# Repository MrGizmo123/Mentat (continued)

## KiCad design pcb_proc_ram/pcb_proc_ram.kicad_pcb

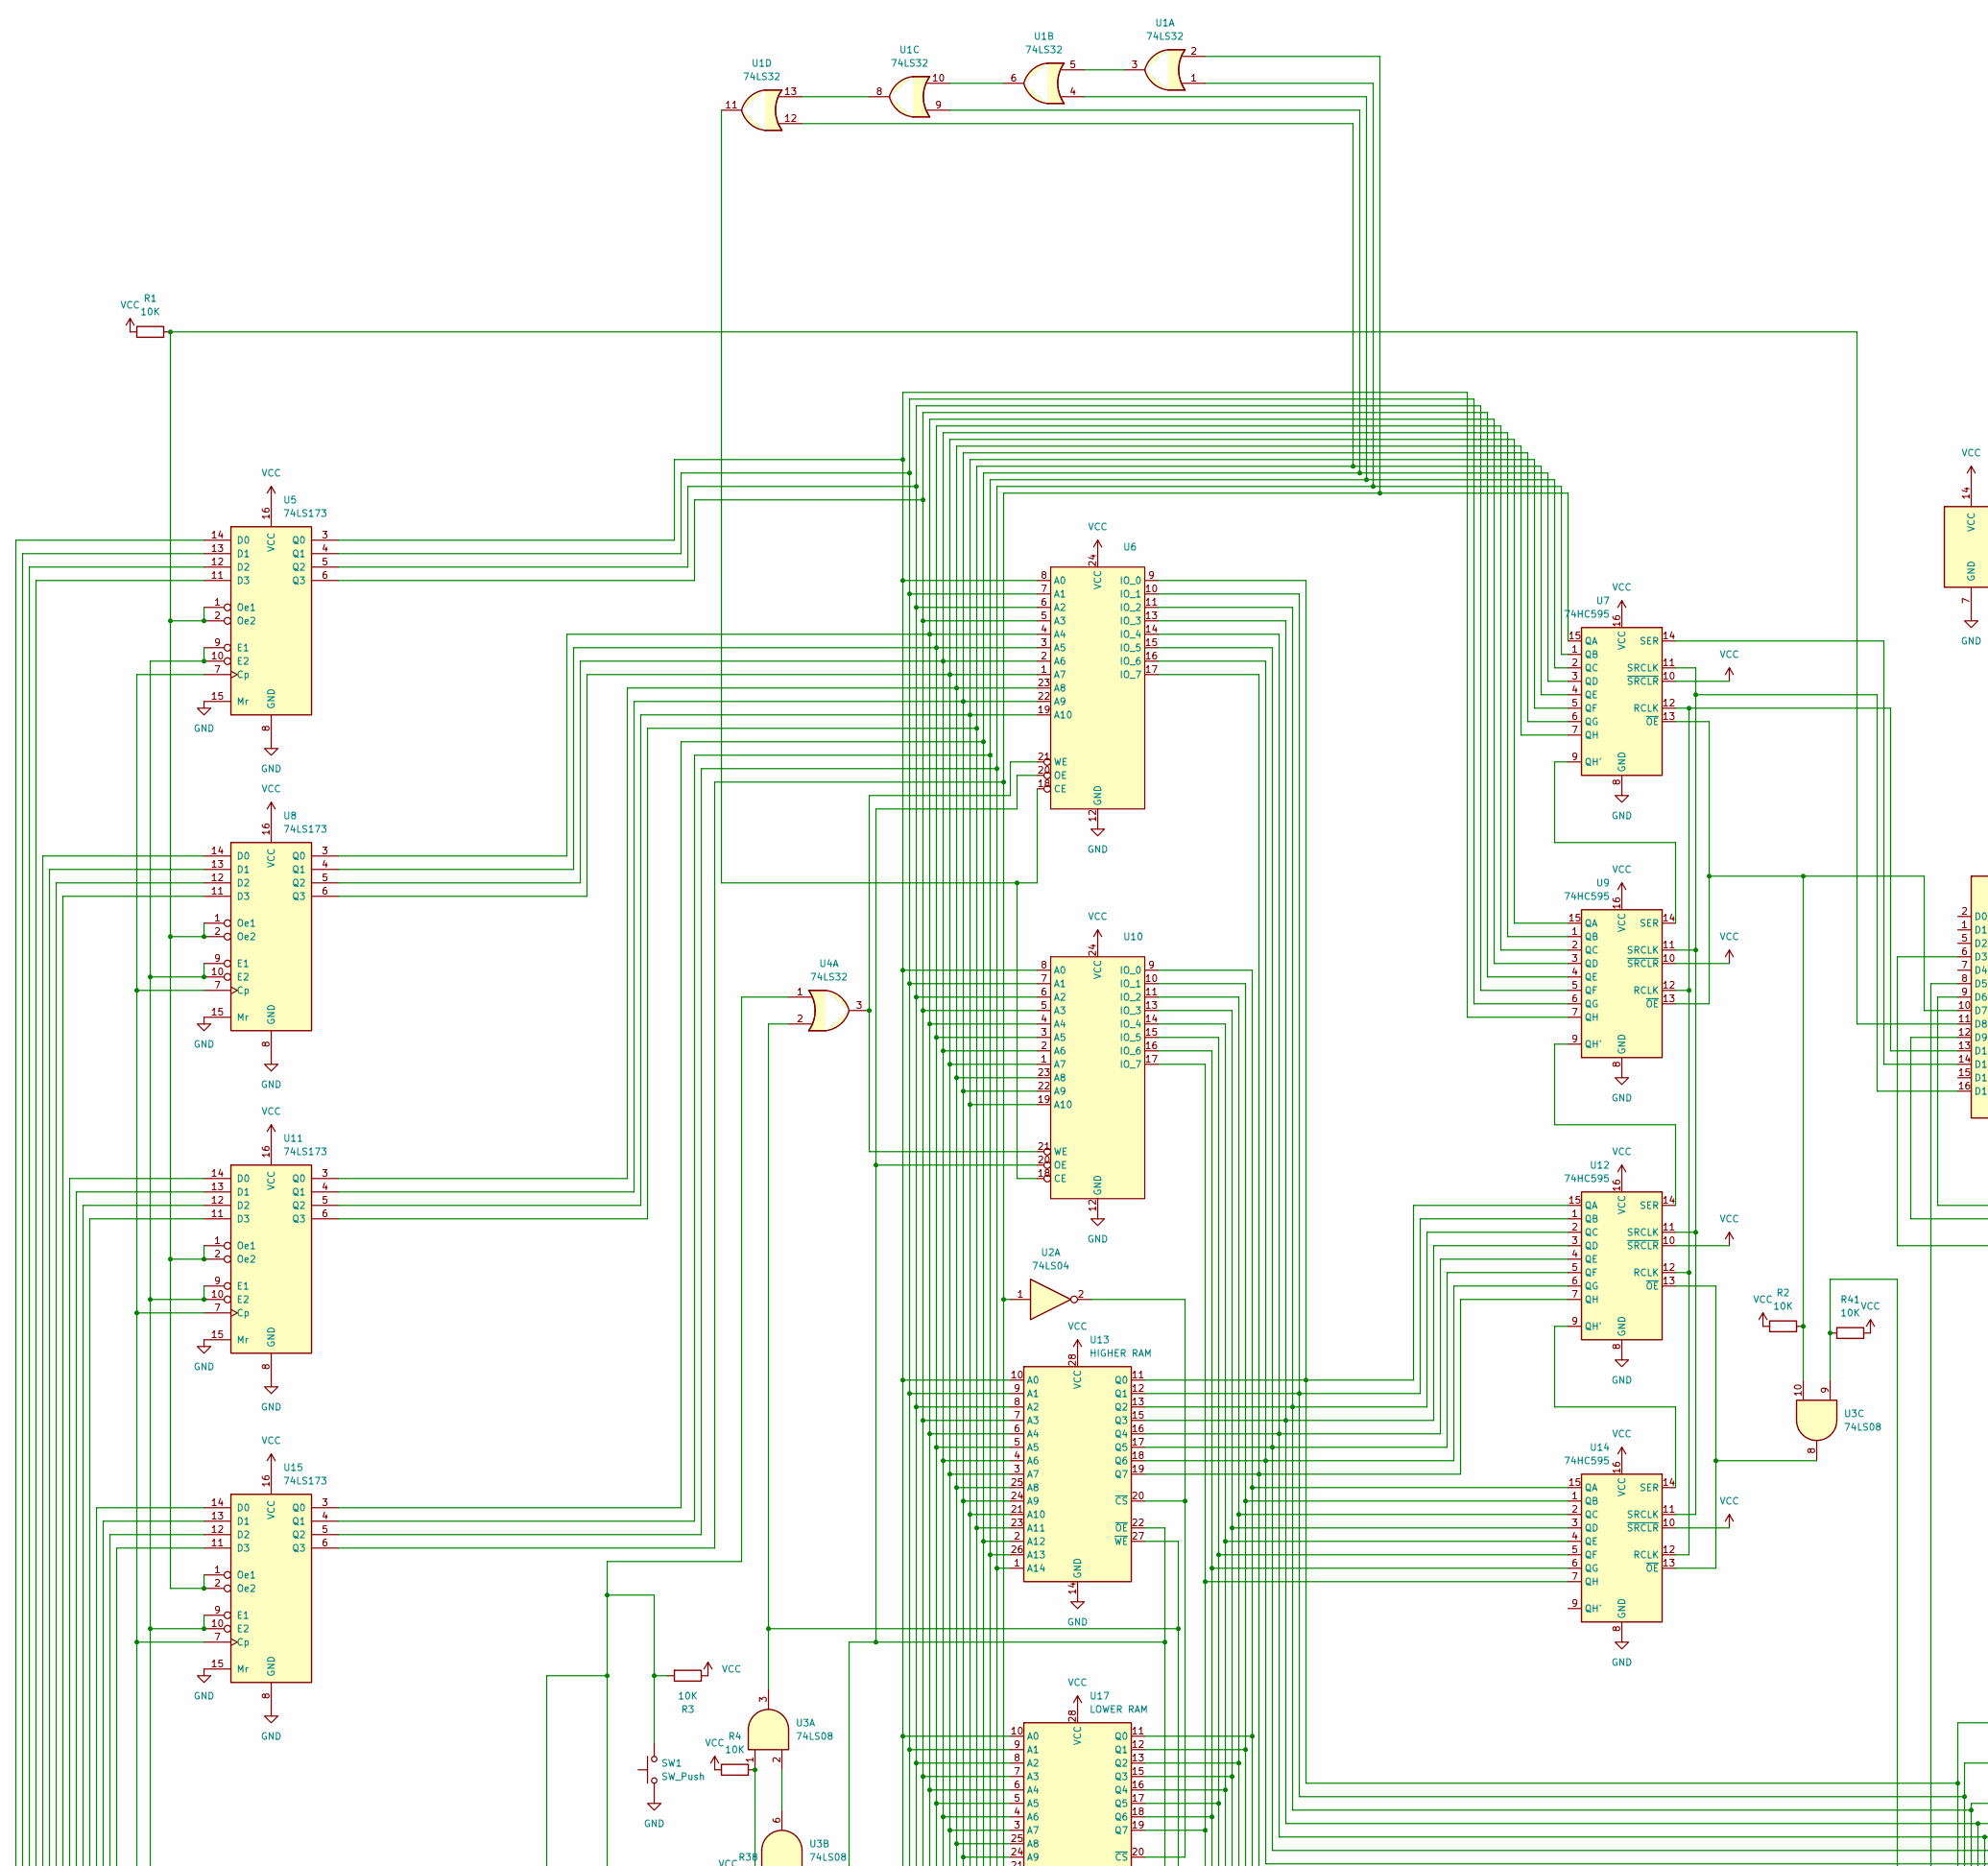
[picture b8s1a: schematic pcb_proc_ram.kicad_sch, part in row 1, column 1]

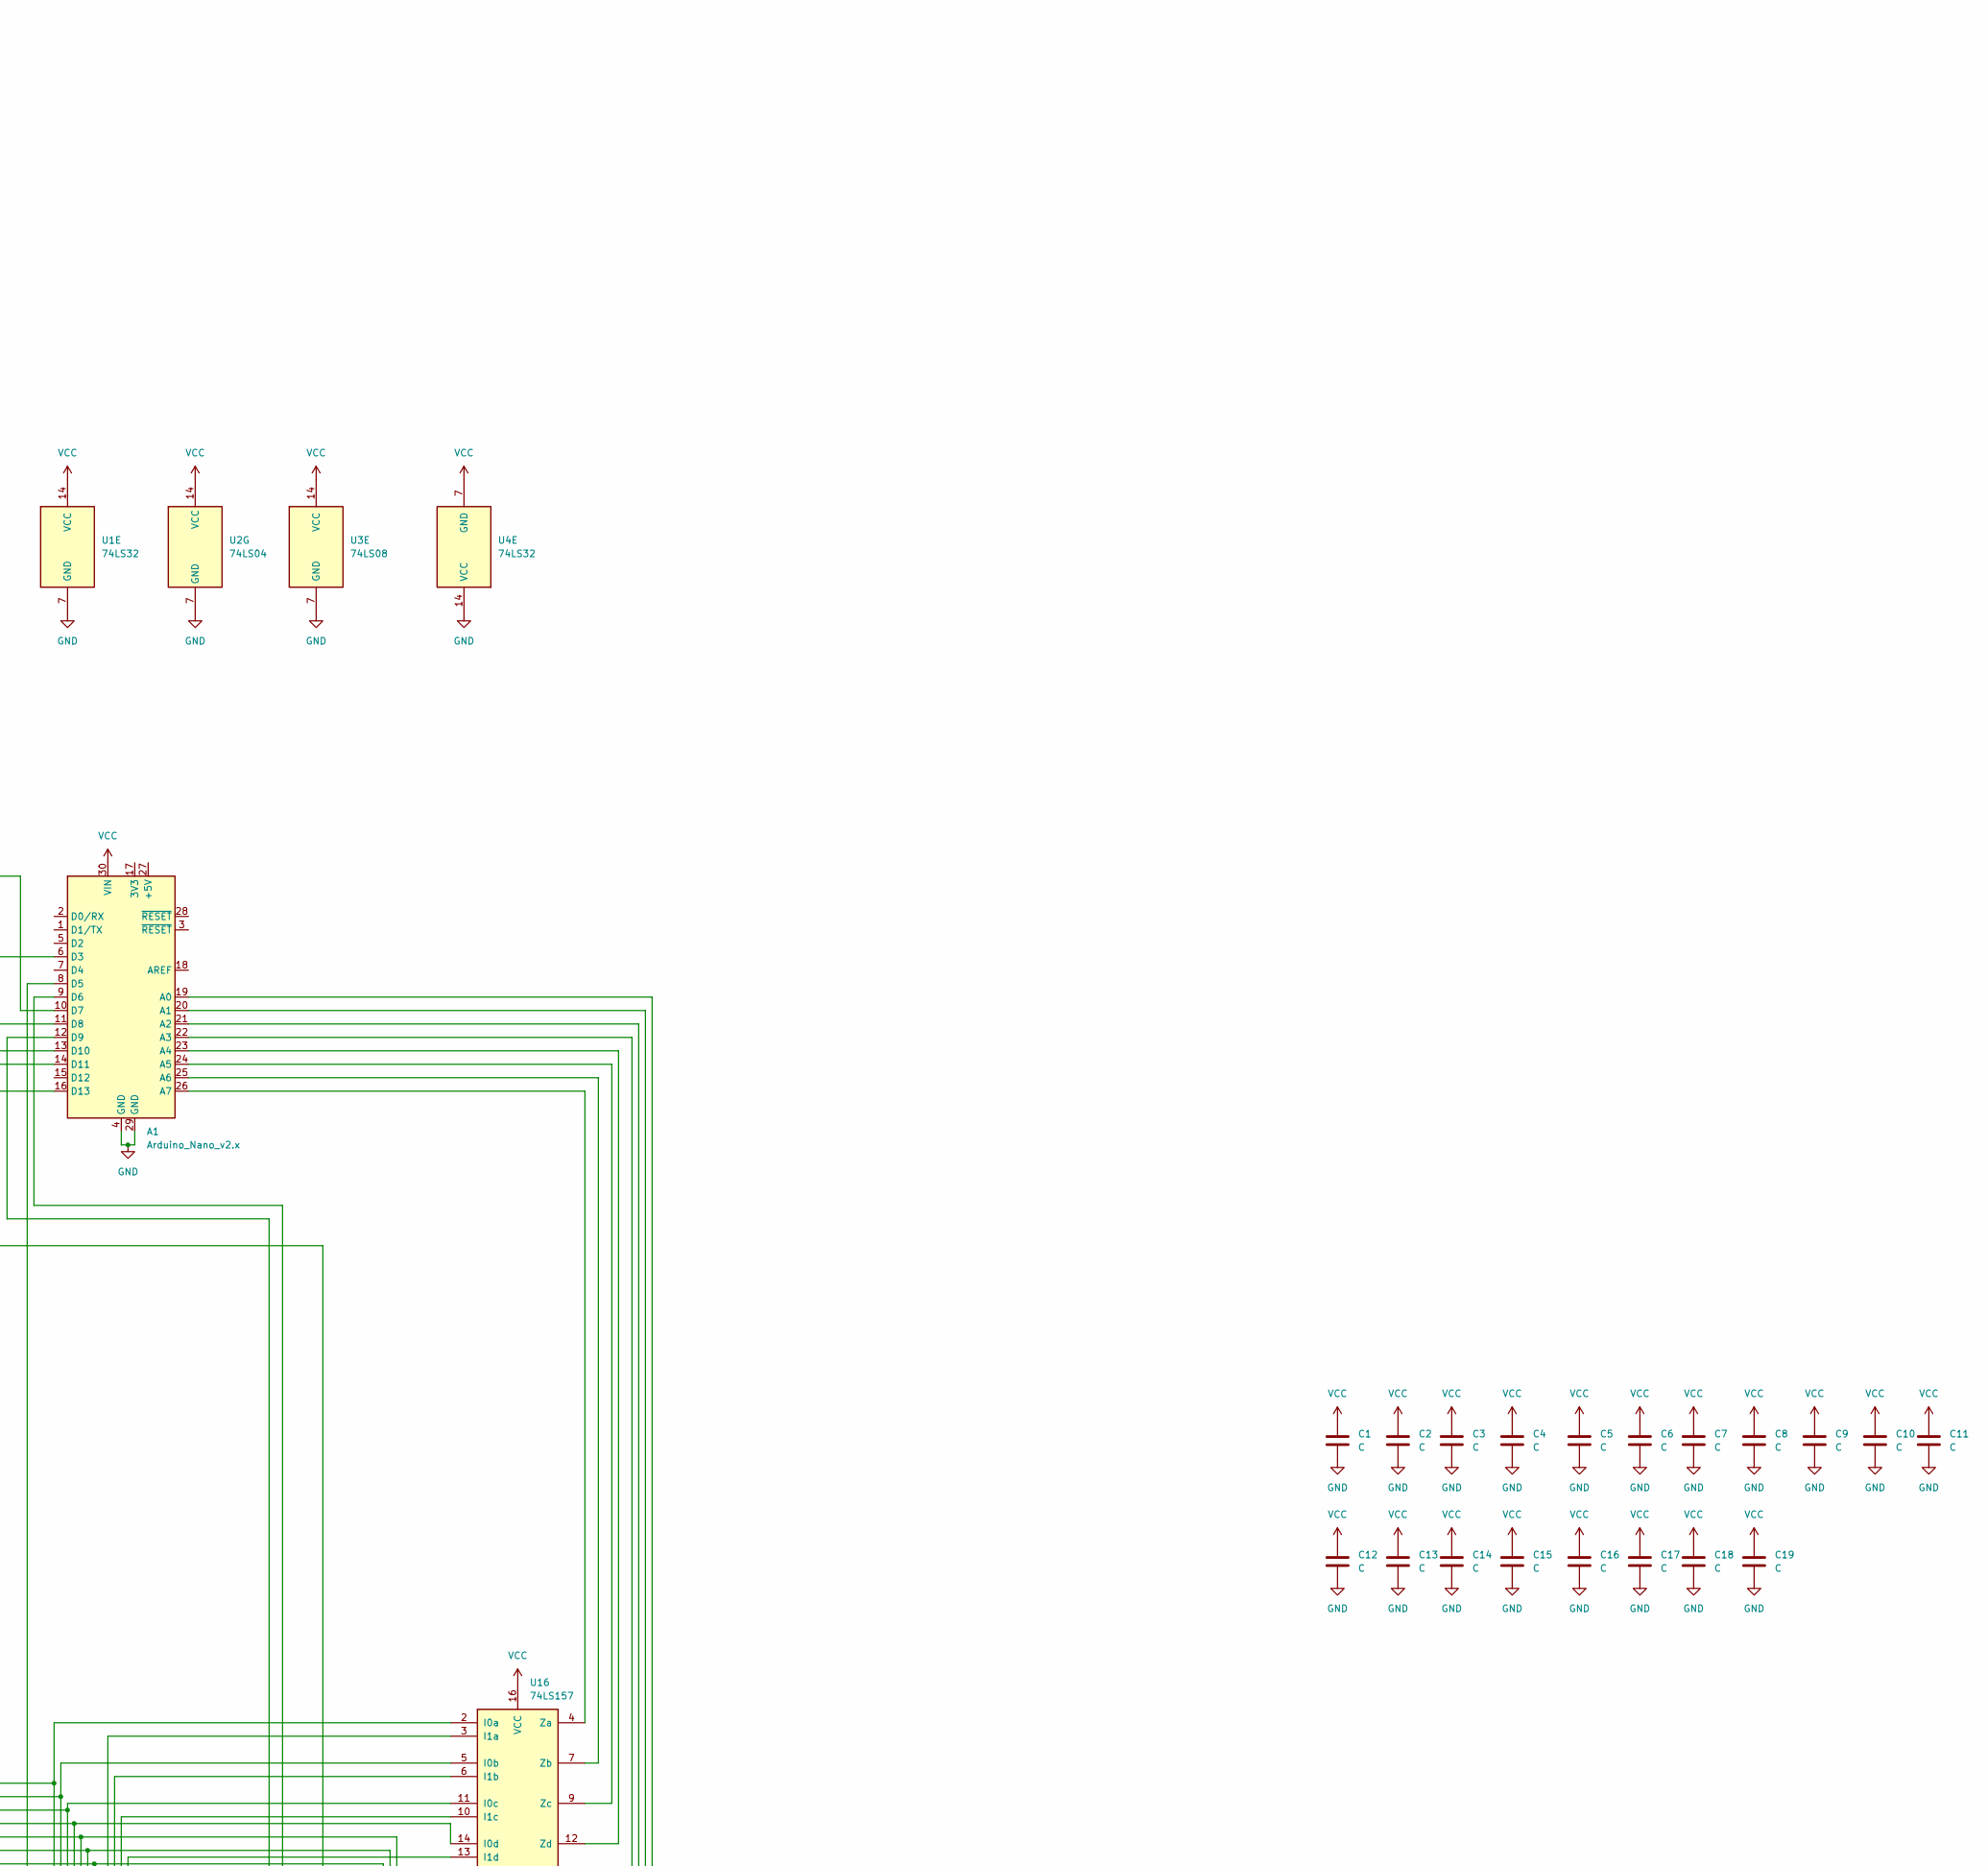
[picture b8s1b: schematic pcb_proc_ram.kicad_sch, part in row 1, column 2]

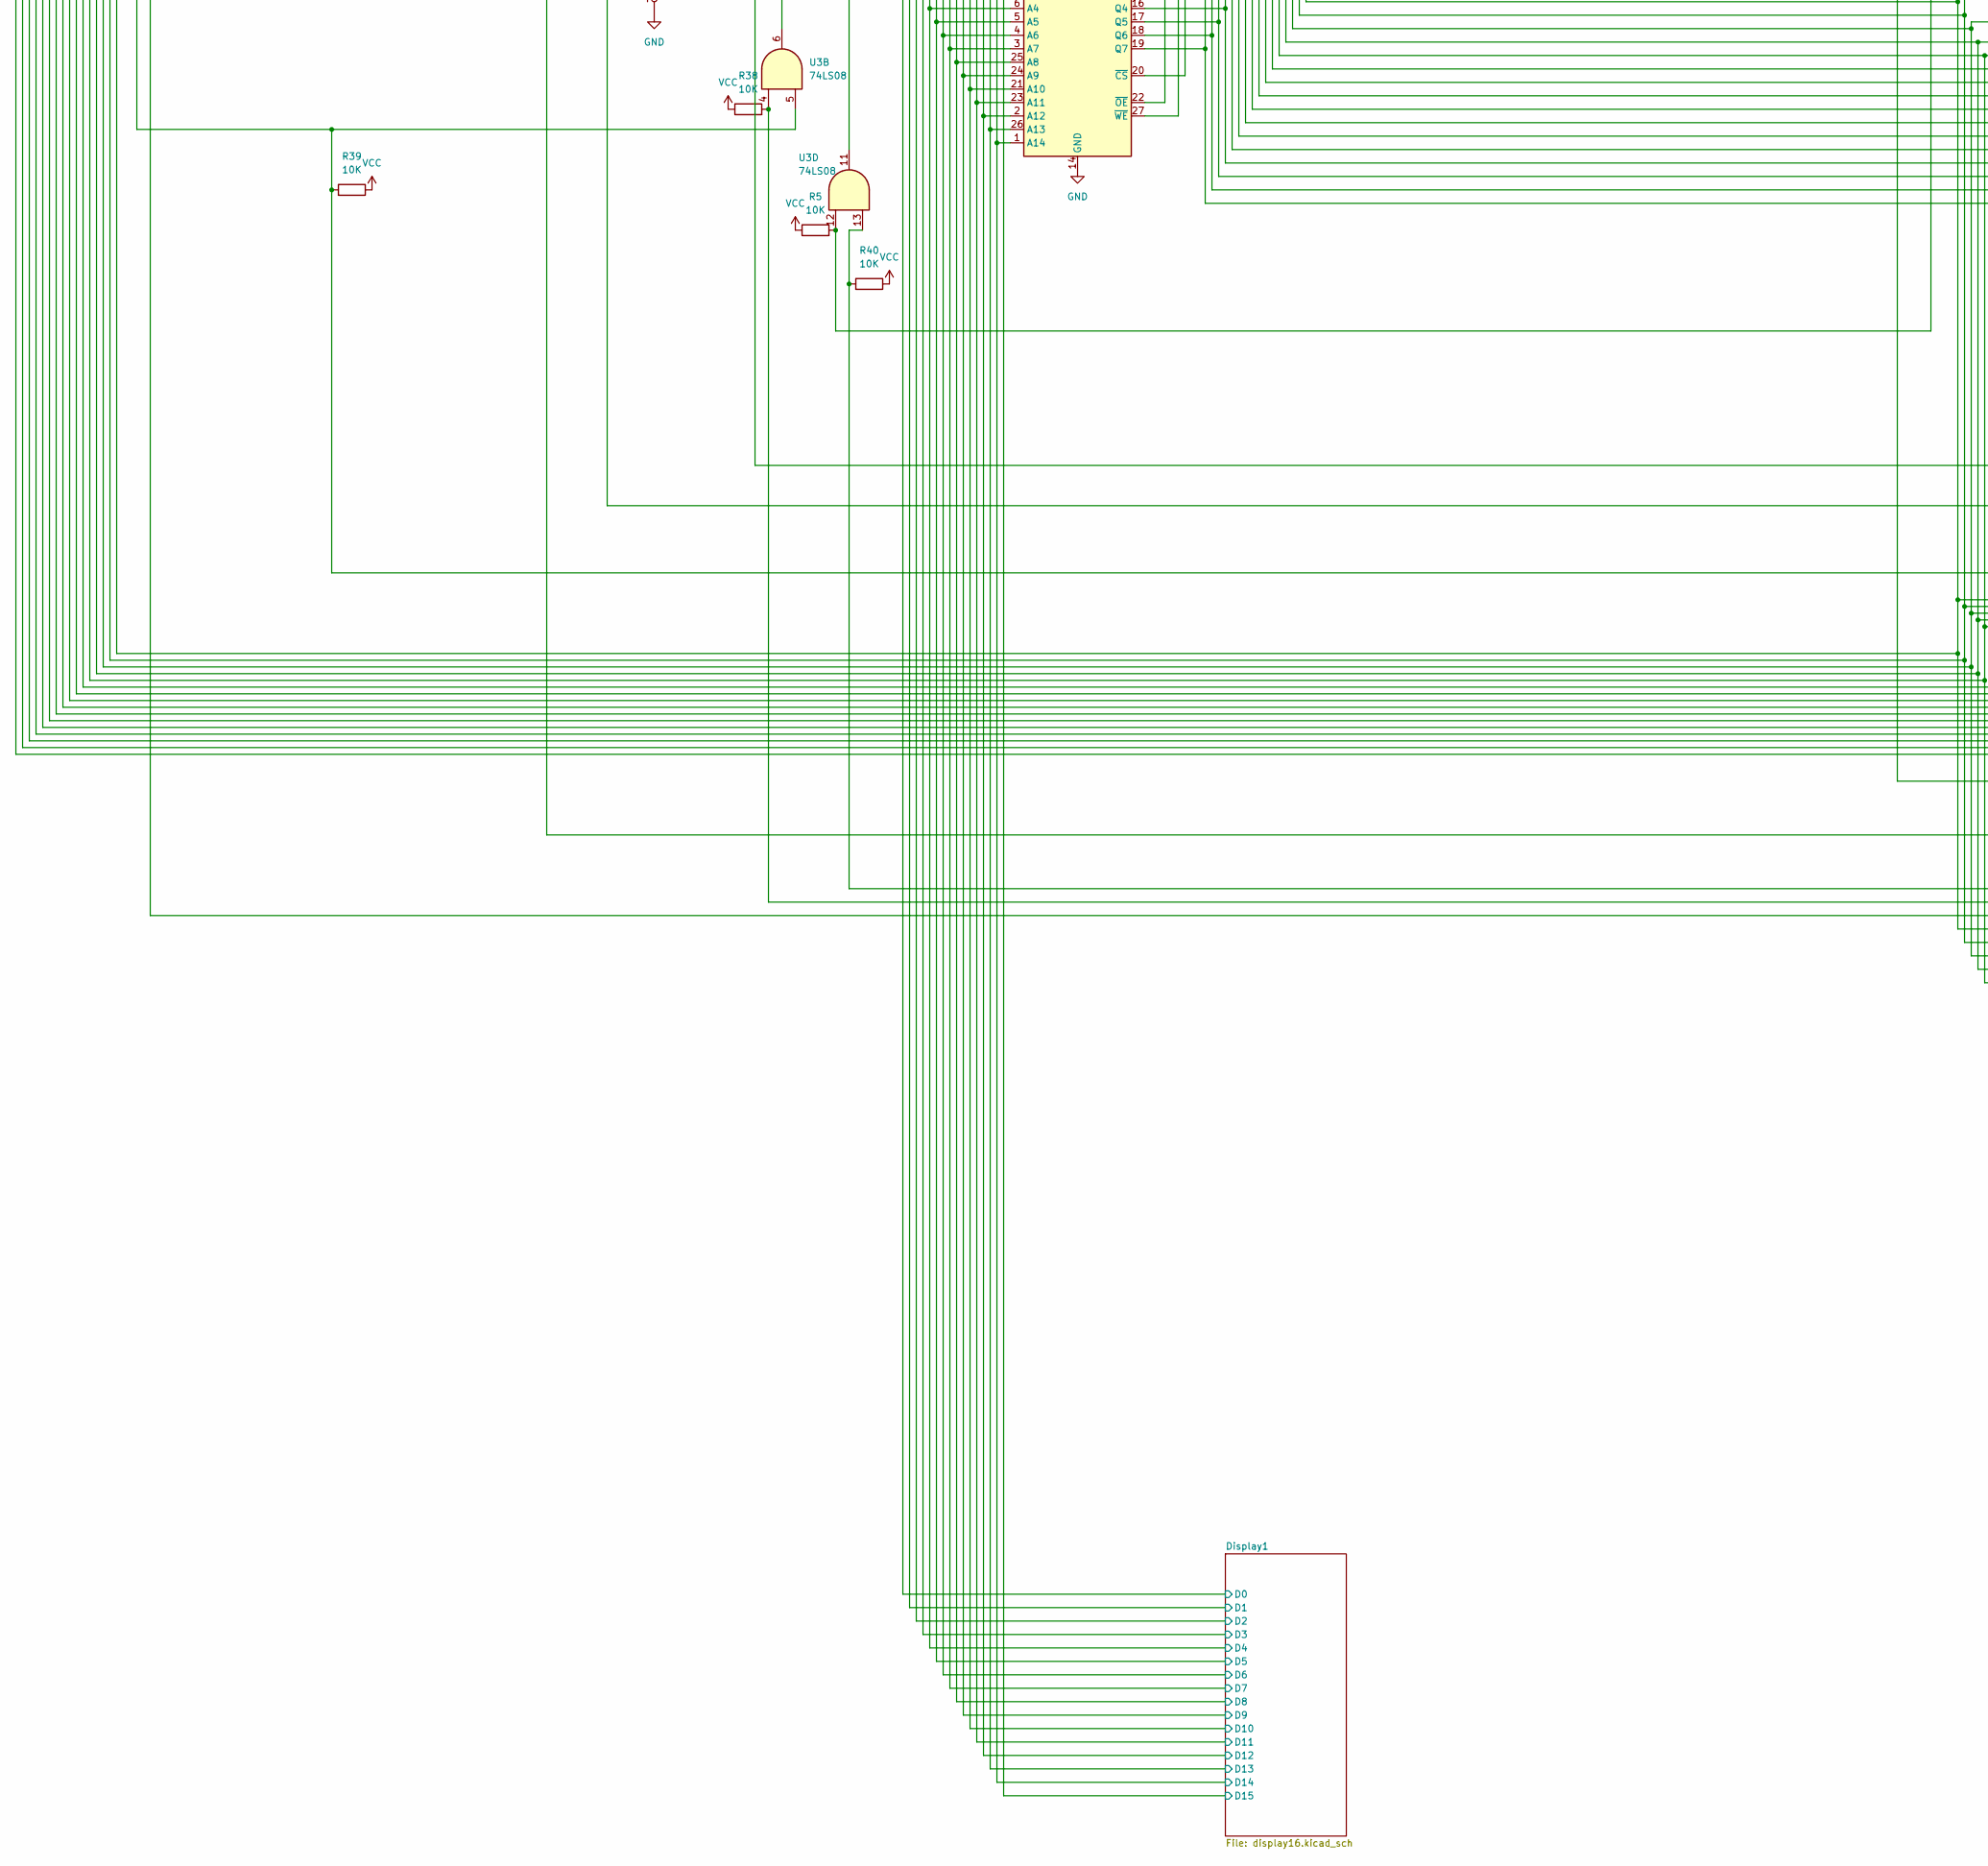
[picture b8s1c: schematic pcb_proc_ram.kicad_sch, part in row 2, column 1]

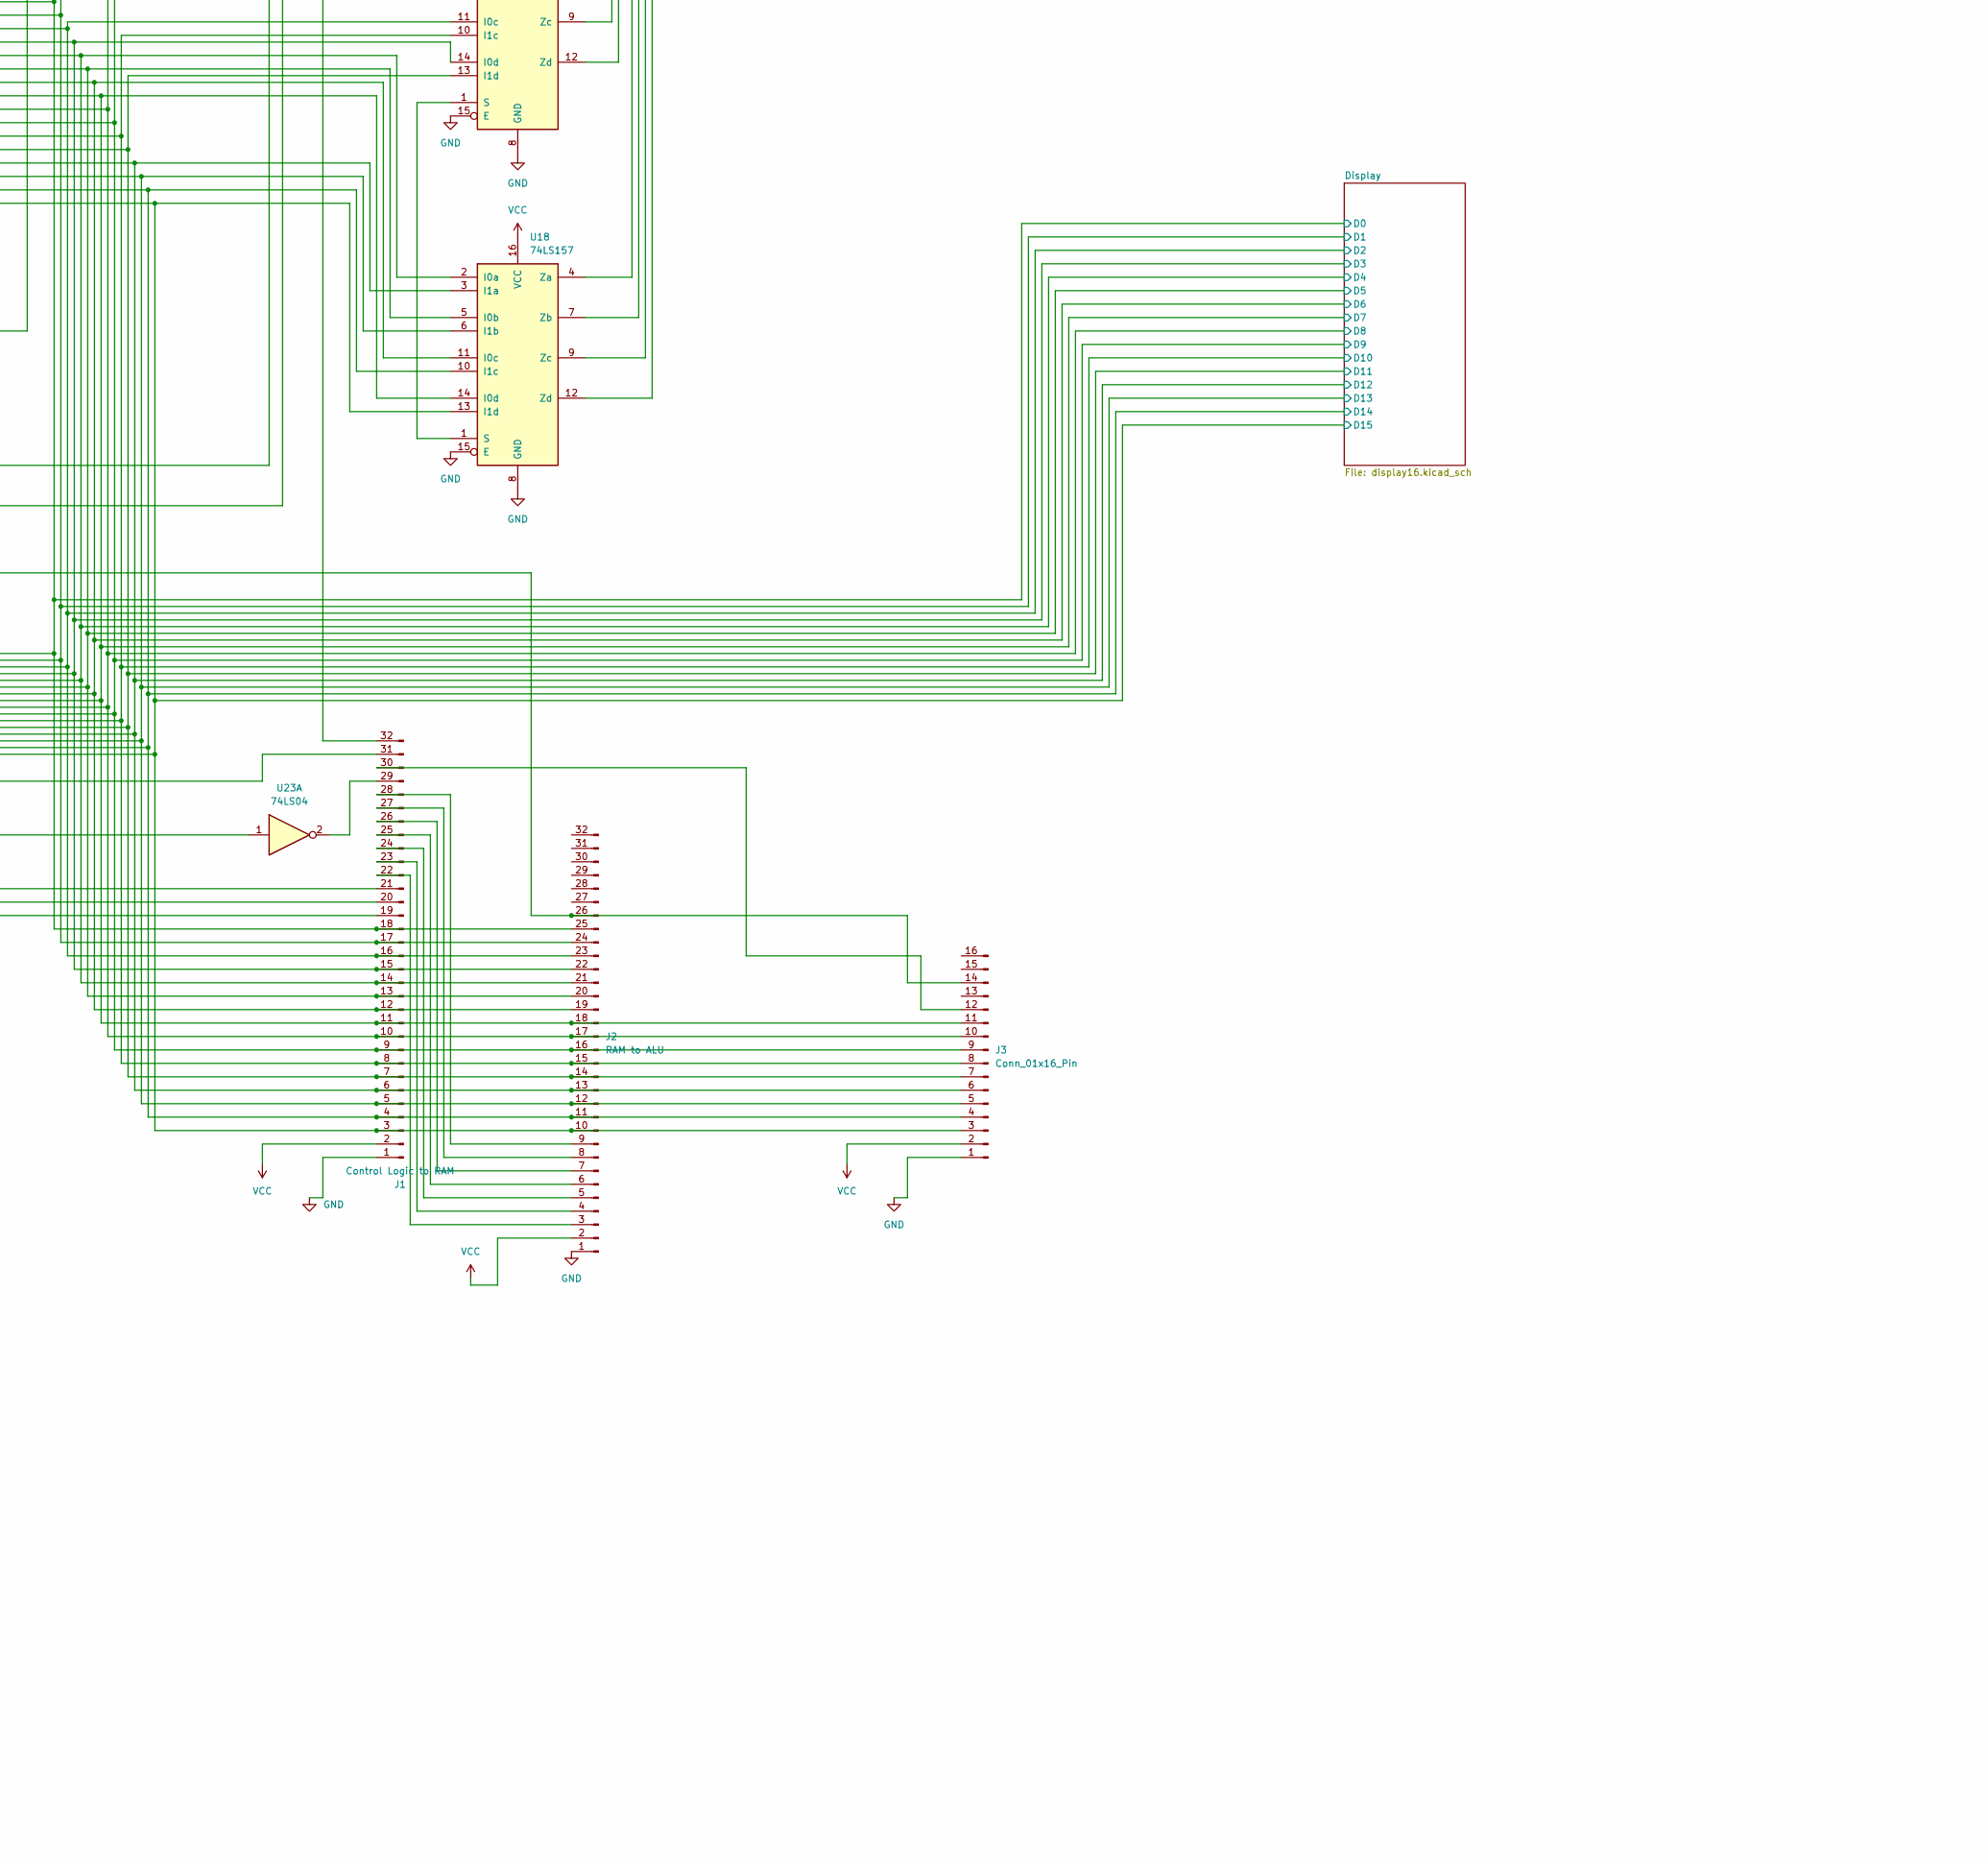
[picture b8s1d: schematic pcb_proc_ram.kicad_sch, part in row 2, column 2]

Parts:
A1: Arduino_Nano_v2.x; Arduino_Nano
C1, C2, C3, C4, C5, C6, C7, C8, C9, C10, C11, C12, C13, C14, C15, C16, C17, C18, C19: C; C_0805_2012Metric
J1: Control Logic to RAM; PinHeader_2x16_P2.54mm_Vertical
J2: RAM to ALU; PinHeader_2x16_P2.54mm_Vertical
J3: Conn_01x16_Pin; PinHeader_1x16_P2.54mm_Vertical
R1, R2, R3, R4, R5, R38, R39, R40, R41: 10K; R_0805_2012Metric
SW1: SW_Push; SW_E-Switch_EG1271_SPDT
U1, U4: 74LS32; DIP-14_W7.62mm_Socket_LongPads
U2, U23: 74LS04; DIP-14_W7.62mm_Socket_LongPads
U3: 74LS08; DIP-14_W7.62mm_Socket_LongPads
U5, U8, U11, U15: 74LS173; DIP-16_W7.62mm_Socket_LongPads
U6, U10: DIP-24_W15.24mm_Socket_LongPads
U7, U9, U12, U14: 74HC595; DIP-16_W7.62mm_Socket_LongPads
U13: HIGHER RAM; DIP-28_W15.24mm_Socket_LongPads
U16, U18: 74LS157; DIP-16_W7.62mm_Socket_LongPads
U17: LOWER RAM; DIP-28_W15.24mm_Socket_LongPads

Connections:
/Display1/D0: U5.3 (Q0), U6.8 (A0), U9.7 (QH), U10.8 (A0), U13.10 (A0), U17.10 (A0); also elsewhere on the board
/Display1/D1: U5.4 (Q1), U6.7 (A1), U9.6 (QG), U10.7 (A1), U13.9 (A1), U17.9 (A1); also elsewhere on the board
/Display1/D2: U5.5 (Q2), U6.6 (A2), U9.5 (QF), U10.6 (A2), U13.8 (A2), U17.8 (A2); also elsewhere on the board
/Display1/D3: U5.6 (Q3), U6.5 (A3), U9.4 (QE), U10.5 (A3), U13.7 (A3), U17.7 (A3); also elsewhere on the board
/Display1/D4: U6.4 (A4), U8.3 (Q0), U9.3 (QD), U10.4 (A4), U13.6 (A4), U17.6 (A4); also elsewhere on the board
/Display1/D5: U6.3 (A5), U8.4 (Q1), U9.2 (QC), U10.3 (A5), U13.5 (A5), U17.5 (A5); also elsewhere on the board
/Display1/D6: U6.2 (A6), U8.5 (Q2), U9.1 (QB), U10.2 (A6), U13.4 (A6), U17.4 (A6); also elsewhere on the board
/Display1/D7: U6.1 (A7), U8.6 (Q3), U9.15 (QA), U10.1 (A7), U13.3 (A7), U17.3 (A7); also elsewhere on the board
/Display1/D8: U6.23 (A8), U7.7 (QH), U10.23 (A8), U11.3 (Q0), U13.25 (A8), U17.25 (A8); also elsewhere on the board
/Display1/D9: U6.22 (A9), U7.6 (QG), U10.22 (A9), U11.4 (Q1), U13.24 (A9), U17.24 (A9); also elsewhere on the board
/Display1/D10: U6.19 (A10), U7.5 (QF), U10.19 (A10), U11.5 (Q2), U13.21 (A10), U17.21 (A10); also elsewhere on the board
/Display1/D11: U1.12, U7.4 (QE), U11.6 (Q3), U13.23 (A11), U17.23 (A11); also elsewhere on the board
/Display1/D12: U1.9, U7.3 (QD), U13.2 (A12), U15.3 (Q0), U17.2 (A12); also elsewhere on the board
/Display1/D13: U1.4, U7.2 (QC), U13.26 (A13), U15.4 (Q1), U17.26 (A13); also elsewhere on the board
/Display1/D14: U1.1, U7.1 (QB), U13.1 (A14), U15.5 (Q2), U17.1 (A14); also elsewhere on the board
/Display1/D15: U1.2, U2.1, U7.15 (QA), U15.6 (Q3); also elsewhere on the board
/Display/D0: J1.18, J2.25, U6.9 (IO_0), U12.15 (QA), U13.11 (Q0), U15.11 (D3), U16.2 (I0a); also elsewhere on the board
/Display/D1: J1.17, J2.24, U6.10 (IO_1), U12.1 (QB), U13.12 (Q1), U15.12 (D2), U16.5 (I0b); also elsewhere on the board
/Display/D2: J1.16, J2.23, U6.11 (IO_2), U12.2 (QC), U13.13 (Q2), U15.13 (D1), U16.11 (I0c); also elsewhere on the board
/Display/D3: J1.15, J2.22, U6.13 (IO_3), U12.3 (QD), U13.15 (Q3), U15.14 (D0), U16.14 (I0d); also elsewhere on the board
/Display/D4: J1.14, J2.21, U6.14 (IO_4), U11.11 (D3), U12.4 (QE), U13.16 (Q4), U18.2 (I0a); also elsewhere on the board
/Display/D5: J1.13, J2.20, U6.15 (IO_5), U11.12 (D2), U12.5 (QF), U13.17 (Q5), U18.5 (I0b); also elsewhere on the board
/Display/D6: J1.12, J2.19, U6.16 (IO_6), U11.13 (D1), U12.6 (QG), U13.18 (Q6), U18.11 (I0c); also elsewhere on the board
/Display/D7: J1.11, J2.18, J3.11, U6.17 (IO_7), U11.14 (D0), U12.7 (QH), U13.19 (Q7), U18.14 (I0d); also elsewhere on the board
/Display/D8: J1.10, J2.17, J3.10, U8.11 (D3), U10.9 (IO_0), U14.15 (QA), U16.3 (I1a), U17.11 (Q0); also elsewhere on the board
/Display/D9: J1.9, J2.16, J3.9, U8.12 (D2), U10.10 (IO_1), U14.1 (QB), U16.6 (I1b), U17.12 (Q1); also elsewhere on the board
/Display/D10: J1.8, J2.15, J3.8, U8.13 (D1), U10.11 (IO_2), U14.2 (QC), U16.10 (I1c), U17.13 (Q2); also elsewhere on the board
/Display/D11: J1.7, J2.14, J3.7, U8.14 (D0), U10.13 (IO_3), U14.3 (QD), U16.13 (I1d), U17.15 (Q3); also elsewhere on the board
/Display/D12: J1.6, J2.13, J3.6, U5.11 (D3), U10.14 (IO_4), U14.4 (QE), U17.16 (Q4), U18.3 (I1a); also elsewhere on the board
/Display/D13: J1.5, J2.12, J3.5, U5.12 (D2), U10.15 (IO_5), U14.5 (QF), U17.17 (Q5), U18.6 (I1b); also elsewhere on the board
/Display/D14: J1.4, J2.11, J3.4, U5.13 (D1), U10.16 (IO_6), U14.6 (QG), U17.18 (Q6), U18.10 (I1c); also elsewhere on the board
/Display/D15: J1.3, J2.10, J3.3, U5.14 (D0), U10.17 (IO_7), U14.7 (QH), U17.19 (Q7), U18.13 (I1d); also elsewhere on the board
GND: A1.4 (GND), A1.29 (GND), C1.2, C2.2, C3.2, C4.2, C5.2, C6.2, C7.2, C8.2, C9.2, C10.2, C11.2, C12.2, C13.2, C14.2, C15.2, C16.2, C17.2, C18.2, C19.2, J1.1, J2.1, J3.1, SW1.1, U1.7 (GND), U2.7 (GND), U3.7 (GND), U4.14 (VCC), U5.8 (GND), U5.15 (Mr), U6.12 (GND), U7.8 (GND), U8.8 (GND), U8.15 (Mr), U9.8 (GND), U10.12 (GND), U11.8 (GND), U11.15 (Mr), U12.8 (GND), U13.14 (GND), U14.8 (GND), U15.8 (GND), U15.15 (Mr), U16.8 (GND), U16.15 (E), U17.14 (GND), U18.8 (GND), U18.15 (E); also elsewhere on the board
unnamed: A1.19 (A0), U18.12 (Zd)
unnamed: A1.20 (A1), U18.9 (Zc)
unnamed: A1.21 (A2), U18.7 (Zb)
unnamed: A1.22 (A3), U18.4 (Za)
unnamed: A1.23 (A4), U16.12 (Zd)
unnamed: A1.24 (A5), U16.9 (Zc)
unnamed: A1.25 (A6), U16.7 (Zb)
unnamed: A1.26 (A7), U16.4 (Za)
unnamed: A1.6 (D3), J1.32
unnamed: A1.8 (D5), R5.2, U3.12
unnamed: A1.9 (D6), R3.2, SW1.2, U4.1, U23.1
unnamed: A1.10 (D7), R2.2, U3.10, U7.13 (~OE), U9.13 (~OE)
unnamed: A1.11 (D8), R1.2, U5.1 (Oe1), U5.2 (Oe2), U8.1 (Oe1), U8.2 (Oe2), U11.1 (Oe1), U11.2 (Oe2), U15.1 (Oe1), U15.2 (Oe2)
unnamed: A1.12 (D9), R4.2, U3.1
unnamed: A1.13 (D10), U7.12 (RCLK), U9.12 (RCLK), U12.12 (RCLK), U14.12 (RCLK)
unnamed: A1.14 (D11), U7.14 (SER)
unnamed: A1.16 (D13), U7.11 (SRCLK), U9.11 (SRCLK), U12.11 (SRCLK), U14.11 (SRCLK)
unnamed: J1.19, U5.9 (E1), U5.10 (E2), U8.9 (E1), U8.10 (E2), U11.9 (E1), U11.10 (E2), U15.9 (E1), U15.10 (E2)
unnamed: J1.20, R38.2, U3.4
unnamed: J1.21, R40.2, U3.13
unnamed: J1.22, J2.3
unnamed: J1.23, J2.4
unnamed: J1.24, J2.5
unnamed: J1.25, J2.6
unnamed: J1.26, J2.7
unnamed: J1.27, J2.8
unnamed: J1.28, J2.9
unnamed: J1.29, U23.2
unnamed: J1.30, J3.12
unnamed: J1.31, R41.2, U3.9
unnamed: J2.26, J3.14, R39.2, U3.5, U5.7 (Cp), U8.7 (Cp), U11.7 (Cp), U15.7 (Cp)
unnamed: U1.3, U1.5
unnamed: U1.6, U1.10
unnamed: U1.8, U1.13
unnamed: U3.2, U3.6
unnamed: U7.9 (QH'), U9.14 (SER)
unnamed: U1.11, U6.18 (CE), U10.18 (CE)
unnamed: U3.11, U6.20 (OE), U10.20 (OE), U13.22 (~OE), U17.22 (~OE)
unnamed: U4.3, U6.21 (WE), U10.21 (WE)
unnamed: U12.9 (QH'), U14.14 (SER)
unnamed: U9.9 (QH'), U12.14 (SER)
unnamed: U3.8, U12.13 (~OE), U14.13 (~OE)
unnamed: U2.2, U13.20 (~CS), U17.20 (~CS)
unnamed: U3.3, U4.2, U13.27 (~WE), U17.27 (~WE)
unnamed: U16.1 (S), U18.1 (S)
VCC: A1.30 (VIN), C1.1, C2.1, C3.1, C4.1, C5.1, C6.1, C7.1, C8.1, C9.1, C10.1, C11.1, C12.1, C13.1, C14.1, C15.1, C16.1, C17.1, C18.1, C19.1, J1.2, J2.2, J3.2, R1.1, R2.1, R3.1, R4.1, R5.1, R38.1, R39.1, R40.1, R41.1, U1.14 (VCC), U2.14 (VCC), U3.14 (VCC), U4.7 (GND), U5.16 (VCC), U6.24 (VCC), U7.10 (~SRCLR), U7.16 (VCC), U8.16 (VCC), U9.10 (~SRCLR), U9.16 (VCC), U10.24 (VCC), U11.16 (VCC), U12.10 (~SRCLR), U12.16 (VCC), U13.28 (VCC), U14.10 (~SRCLR), U14.16 (VCC), U15.16 (VCC), U16.16 (VCC), U17.28 (VCC), U18.16 (VCC); also elsewhere on the board
